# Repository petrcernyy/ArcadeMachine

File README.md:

# Educational Arcade Machine

Students studying first year of mechatronics at BUT have MATLAB course. In addition to the course they can program their own minigame, like PONG, Snake, with the help of teacher. This project should increase motivation of students for programming their own game. 

For this project an arcade machine like device was created. For this device an application that allows importing games from students, manages games and student profiles and displays games was created.

Also a PCB that monitors a state of buttons and joystick used for playing games was designed. PCB also communicates with RFID reader that allows reading ID of student's ISIC cards.

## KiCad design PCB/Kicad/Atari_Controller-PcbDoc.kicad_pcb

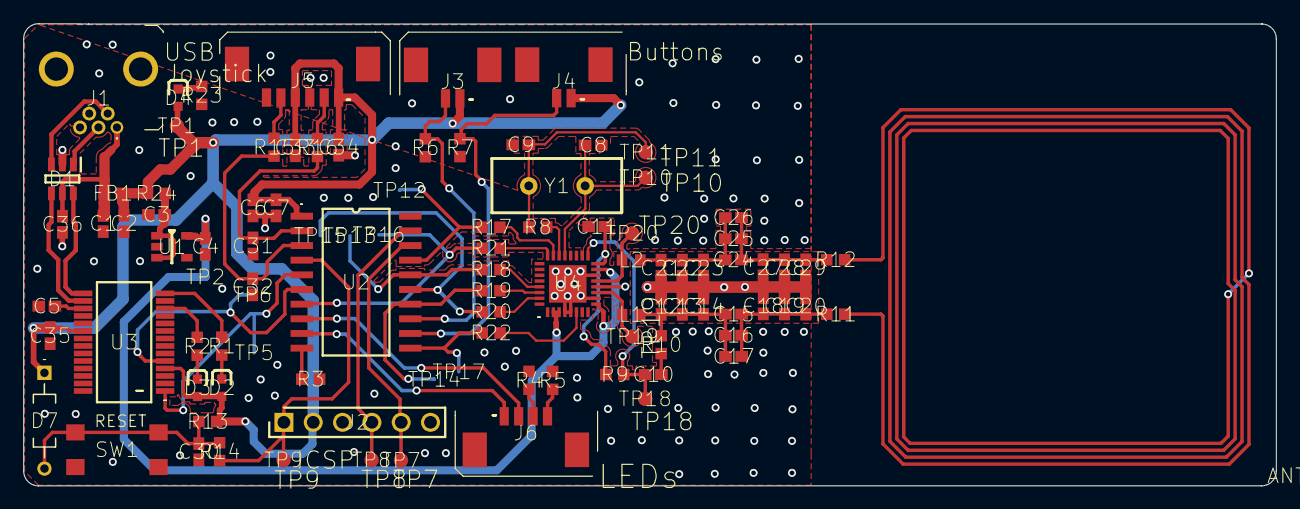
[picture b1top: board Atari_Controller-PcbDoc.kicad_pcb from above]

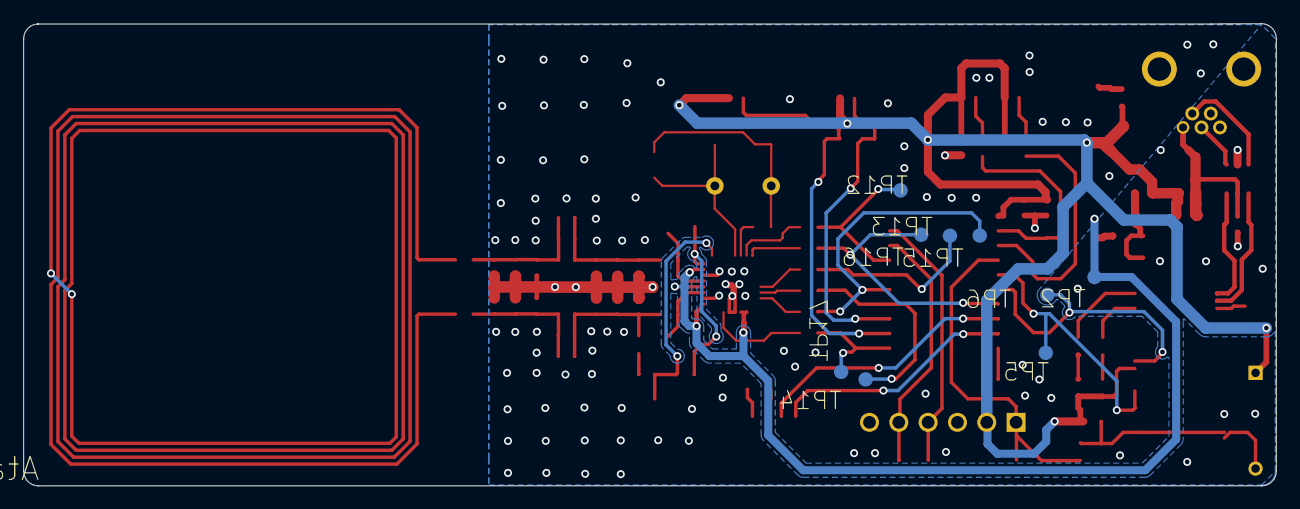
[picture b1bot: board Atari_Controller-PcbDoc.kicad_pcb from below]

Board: 2 copper layers, 108.5 x 40.0 mm, 99 parts (10 on the bottom side), 57 nets.

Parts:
ANT1: ANT1; RFID_Antenna
C1: C1; CAP_0603
C2: C2; CAP_0603
C3: C3; CAP_0603
C4: C4; CAP_0603
C5: C5; CAP_0603
C6: C6; CAP_0603
C7: C7; CAP_0603
C8: C8; CAP_0603
C9: C9; CAP_0603
C10: C10; CAP_0603
C11: C11; CAP_0603
C12: C12; CAP_0603
C13: C13; CAP_0603
C14: C14; CAP_0603
C15: C15; CAP_0603
C16: C16; CAP_0603
C17: C17; CAP_0603
C18: C18; CAP_0603
C19: C19; CAP_0603
C20: C20; CAP_0603
C21: C21; CAP_0603
C22: C22; CAP_0603
C23: C23; CAP_0603
C24: C24; CAP_0603
C25: C25; CAP_0603
C26: C26; CAP_0603
C27: C27; CAP_0603
C28: C28; CAP_0603
C29: C29; CAP_0603
C30: C30; CAP_0603
C31: C31; CAP_0603
C32: C32; CAP_0603
C33: C33; CAP_0603
C34: C34; CAP_0603
C35: C35; CAP_0603
C36: C36; CAP_0603
D1: D1; SOT-666
D2: D2; LED_0603
D3: D3; LED_0603
D4: D4; LED_0603
D7: D7; 1N4148
FB1: FB1; Ferrite_Bead_0603
J1: J1; USB-B-MINI
J2: J2; 6_pin_2.54
J3: J3; Molex_Picoblade_2pin
J4: J4; Molex_Picoblade_2pin
J5: J5; Molex_Picoblade_6pin
J6: J6; MOLEX_PICOBLADE_4Pin
L1: L1; IND_0603
L2: L2; IND_0603
R1: R1; RES_0603
R2: R2; RES_0603
R3: R3; RES_0603
R4: R4; RES_0603
R5: R5; RES_0603
R6: R6; RES_0603
R7: R7; RES_0603
R8: R8; RES_0603
R9: R9; RES_0603
R10: R10; RES_0603
R11: R11; RES_0603
R12: R12; RES_0603
R13: R13; RES_0603
R14: R14; RES_0603
R15: R15; RES_0603
R16: R16; RES_0603
R17: R17; RES_0603
R18: R18; RES_0603
R19: R19; RES_0603
R20: R20; RES_0603
R21: R21; RES_0603
R22: R22; RES_0603
R23: R23; RES_0603
R24: R24; RES_0603
SW1: SW1; Tactile_Switch_4.5x4.5
TP1: TP1; Pad_2.5mm
TP2: TP2; Pad_2.5mm
TP5: TP5; Pad_2.5mm
TP6: TP6; Pad_2.5mm
TP7: TP7; Pad_2.5mm
TP8: TP8; Pad_2.5mm
TP9: TP9; Pad_2.5mm
TP10: TP10; Pad_2.5mm
TP11: TP11; Pad_2.5mm
TP12: TP12; Pad_2.5mm
TP13: TP13; Pad_2.5mm
TP14: TP14; Pad_2.5mm
TP15: TP15; Pad_2.5mm
TP16: TP16; Pad_2.5mm
TP17: TP17; Pad_2.5mm
TP18: TP18; Pad_2.5mm
TP19: TP19; Pad_2.5mm
TP20: TP20; Pad_2.5mm
U1: U1; SOT-23-5
U2: U2; SOP20
U3: U3; SOP65P780X200-28N
U4: U4; PQFN50P500X500X100_HS-33N
Y1: Y1; CrystalOscillator

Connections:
+3V3: C4.2, TP2.1, U1.5, U4.2, U4.3, U4.9, U4.12, U4.15
+5: C2.2, C6.2, C7.2, C33.2, C34.2, C35.2, D2.2, D3.2, D4.2, D7.1, FB1.2, J2.2, J3.1, J4.1, J5.1, J5.4, R13.2, R24.1, TP1.1, U2.1, U3.4, U3.20
+VBUS: C1.2, C36.2, D1.5, FB1.1, J1.1
Button_1: J3.2, R6.2, U2.13
Button_2: J4.2, R7.2, U2.12
Conn_D_N: D1.3, J1.2
Conn_D_P: D1.1, J1.3
FT_3V3OUT: C5.2, U3.17
GND: C1.1, C2.1, C3.1, C4.1, C5.1, C6.1, C7.1, C8.1, C9.1, C11.2, C12.1, C13.1, C14.1, C18.1, C19.1, C20.1, C21.2, C22.2, C23.2, C27.2, C28.2, C29.2, C30.1, C31.1, C32.1, C33.1, C34.1, C35.1, C36.1, D1.2, J1.5, J1.MH1, J1.MH2, J2.3, J5.3, J5.6, R3.1, R4.1, R5.1, R6.1, R7.1, R23.1, SW1.1, U1.2, U2.20, U3.7, U3.18, U3.21, U3.25, U3.26, U4.4, U4.5, U4.10, U4.14, U4.18, U4.33
ICSPCLK: J2.5, TP7.1, U2.18
ICSPDAT: J2.4, TP8.1, U2.19
IRQ: R17.1, TP12.1, U2.17
Joystick_X: C32.2, R15.1, U2.3
Joystick_Y: C31.2, R16.1, U2.2
MCU_LED1: J6.1, U2.9
MCU_LED2: J6.2, U2.8
MCU_RX: TP5.1, U2.5, U3.1
MCU_TX: TP6.1, U2.6, U3.5
MISO: R20.1, TP15.1, U2.15
MOSI: R19.1, TP14.1, U2.14
NRSTPD: R22.2, TP17.1, U2.11
NSS: R21.1, TP16.1, U2.7
NetANT1_1: R11.1, R12.2
NetC3_2: C3.2, R24.2, U1.1, U1.3
NetC9_2: C9.2, R8.1, TP11.1, Y1.2
NetC10_1: C10.1, R10.2
NetC12_2: C12.2, C13.2, C14.2, C15.1, C16.1, C17.1, L1.2, R10.1
NetC15_2: C15.2, C16.2, C17.2, C18.2, C19.2, C20.2, R11.2
NetC21_1: C21.1, C22.1, C23.1, C24.1, C25.1, C26.1, L2.2
NetC24_2: C24.2, C25.2, C26.2, C27.1, C28.1, C29.1, R12.1
NetC30_2: C30.2, D7.2, R13.1, R14.2, SW1.2
NetD2_1: D2.1, R1.2
NetD3_1: D3.1, R2.2
NetD4_1: D4.1, R23.2
NetJ5_2: J5.2, R16.2
NetJ5_5: J5.5, R15.2
NetJ6_3: J6.3, R4.2
NetJ6_4: J6.4, R5.2
NetR1_1: R1.1, U3.14
NetR2_1: R2.1, U3.12
NetR3_2: R3.2, U2.10
RF_IRQ: R17.2, U4.23
RF_MISO: R20.2, U4.31
RF_MOSI: R19.2, U4.30
RF_NRSTPD: R22.1, U4.6
RF_NSS: R21.2, U4.24
RF_OSCIN: C8.2, TP10.1, U4.21, Y1.1
RF_OSCOUT: R8.2, U4.22
RF_RX: C10.2, R9.2, TP18.1, U4.17
RF_SCK: R18.2, U4.29
RF_TX1: L1.1, TP19.1, U4.11
RF_TX2: L2.1, TP20.1, U4.13
RF_VMID: C11.1, R9.1, U4.16
SCK: R18.1, TP13.1, U2.16
USB_D_N: D1.4, U3.16
USB_D_P: D1.6, U3.15
~MCLR~: J2.1, R14.1, TP9.1, U2.4

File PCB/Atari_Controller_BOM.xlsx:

Quantity | Designator | Comment | Description | Part ID | LINK
1 | C1 | 10n | Capacitor SMD 0603 16V
2 | C2, C6 | 4u7 | Capacitor SMD 0603 16V
2 | C3, C4 | 1u | Capacitor SMD 0603 16V
10 | C5, C7, C11, C30, C31, C32, C33, C34, C35, C36 | 100n | Capacitor SMD 0603 10V, Capacitor SMD 0603 16V
2 | C8, C9 | 10p | Capacitor SMD 0603 16V
1 | C10 | 1n | Capacitor SMD 0603 16V
2 | C12, C21 | 75p | Capacitor SMD 0603 16V
2 | C13, C22 | 47p | Capacitor SMD 0603 16V
2 | C15, C24 | 39p | Capacitor SMD 0603 16V
2 | C18, C27 | 180p | Capacitor SMD 0603 16V
2 | C19, C28 | 16p | Capacitor SMD 0603 16V
1 | D1 | USBLC6-2SC6 | ESD Suppressors / TVS Diodes ESD Protection Low Cap | USBLC6-2SC6 | https://www.tme.eu/cz/details/usblc6-2sc6/ochranne-diody-sit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
2 | D2, D3 | SMD-GREEN | LED SMD 0603 | OSG50603C1E | https://www.tme.eu/cz/details/osg50603c1e/diody-led-smd-bare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
1 | D4 | SMD-RED | LED SMD 0603 | KPH-1608ID | https://www.tme.eu/cz/details/kph-1608id/diody-led-smd-barev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
1 | D7 | 1N4148 | THT; 100V; 0,2A; Ifsm: 1A; DO35; Ufmax: 1V; 4ns | 1N4148 | https://www.tme.eu/cz/details/1n4148-fai/univerzalni-diody-t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
1 | FB1 | 120R @ 100 MHz | Ferrite Bead 0603 | BLM18PG121SH1D | https://www.tme.eu/en/details/blm18pg121sh1d/ferrite-beads/murata/
1 | J1 | UB-M5BR-DM14-4D | USB-B mini THT | UB-M5BR-DM14-4D (LF)(SN)(L) | https://www.tme.eu/cz/details/ub-m5br-dm14-4d/konektory-usb-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
1 | J2 | ICSP Programmer | 6 pin male header 2.54mm
2 | J3, J4 | 532610271 | Zásuvka; kabel-pl.spoj; vidlice; PicoBlade™; 1,25mm; PIN: 2; SMT; 1A | 532610271 | https://www.tme.eu/cz/details/mx-53261-0271/signalove-konekt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
1 | J5 | 532610671 | Zásuvka; kabel-pl.spoj; vidlice; PicoBlade™; 1,25mm; PIN: 6; SMT; 1A | 532610671 | https://www.tme.eu/cz/details/mx-53261-0671/signalove-konekt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
1 | J6 | 532610471 | Zásuvka; kabel-pl.spoj; vidlice; PicoBlade™; 1,25mm; PIN: 4; SMT; 1A | 532610471 | https://www.tme.eu/cz/details/mx-53261-0471/signalove-konekt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
2 | L1, L2 | 470n | Inductor 0603 SMD | LBCNF1608KKTR47MAD | https://cz.mouser.com/ProductDetail/TAIYO-YUDEN/LBCNF1608KKT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
5 | R1, R2, R4, R5, R23 | 330R | Resistor SMD 0603
7 | R3, R6, R7, R13, R14, R15, R16 | 10k | Resistor SMD 0603
8 | R8, R17, R18, R19, R20, R21, R22, R24 | 0R | Resistor SMD 0603
1 | R9 | 1k | Resistor SMD 0603
1 | R10 | 15k | Resistor SMD 0603
2 | R11, R12 | 1R3 | Resistor SMD 0603
1 | SW1 | SPST_Switch | SPST-NO Tactile Switch 4.5x4.5 | TL3305AF160QG | https://www.tme.eu/cz/details/tl3305af160qg/mikrospinace-tac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
1 | U1 | MIC5504 | LDO regulator 3.3V | MIC5504-3.3YM5-TR | https://cz.mouser.com/ProductDetail/Microchip-Technology/MIC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
1 | U2 | PIC18F15Q40 | PIC18F04/05/14/15Q40 14/20-Pin, Low-Power, High-Performance Microcontroller | PIC18F15Q40-I/SO | https://www.tme.eu/cz/details/pic18f15q40-i_so/rodina-pic-8-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
1 | U3 | FT232RNL | USB Interface IC USB Full Speed to Serial UART IC, Includes Oscillator and EEPR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 | FT232RNL-REEL | https://www.tme.eu/cz/details/ft232rnl/integrovane-obvody-in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
1 | U4 | MFRC52202HN1,115 | NFC/RFID Tags & Transponders Standard performance MIFARE and NTAG frontend | MFRC52202HN1,115 | https://cz.mouser.com/ProductDetail/NXP-Semiconductors/MFRC5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
1 | Y1 | 27.12 MHz | Crystal oscillator | LFXTAL036075Bulk | https://cz.mouser.com/ProductDetail/IQD/LFXTAL036075Bulk?qs=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

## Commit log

2023-11-26 Init commit
2023-11-26 Changed way the controls are sent to user
2023-12-07 Added snake game, changed watchdog timer(in progress)
2023-12-17 Added WatchDog timer for checking infinit loop
2024-01-26 Created Arcade Machine enclosure
2024-01-26 Added zip
2024-01-26 Controller FW Init
2024-01-26 WatchDog Update
2024-01-26 Added gpio functionality
2024-01-26 Added ADC functionality
2024-01-27 Added UART functionality
2024-01-27 Added UART receive interrupt
2024-01-27 Added MRFC library for ISIC
2024-01-31 Update_Working
2024-01-31 Update_2
2024-02-07 Change of buttons
2024-02-07 Update
    WatchdogTimer
2024-02-09 Update
    Change of width -> 16
2024-02-09 Update
    Removed Serial.print from library
2024-02-11 Update
    Added mfrc library, added comments
2024-03-12 Update
    Added Virtual Keyboard
2024-03-23 Update
    Separated into more objects
2024-04-11 Working Anticollision
2024-06-22 Update
    Name change
2024-06-22 Update
    Added pictures
2024-06-22 Added picture
